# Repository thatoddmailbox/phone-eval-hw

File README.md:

# phone-eval-hw
The evaluation board for the [phone I built](https://github.com/thatoddmailbox/phone). [View PDF schematic](./thingb-eval-hw.pdf)

This was the first version of the hardware. The idea was to make sure that things were working in a more open (and therefore easier to assemble/test/debug) design before making a smaller, more portable version. It also allowed some problems to be caught and addressed for the next revision.

There are a [couple of known issues](https://github.com/thatoddmailbox/phone-eval-hw/issues/1) with this hardware. The biggest issue is that the battery charging IC, while theoretically capable of charging the battery at 1A, quickly gets too hot and throttles itself when charging. These issues were fixed in the [next revision](https://github.com/thatoddmailbox/phone-hw), which also had the correct form factor.

(note: this was originally called thingb-eval-hw because I thought I'd come up with a more creative name than "phone". I did not.)

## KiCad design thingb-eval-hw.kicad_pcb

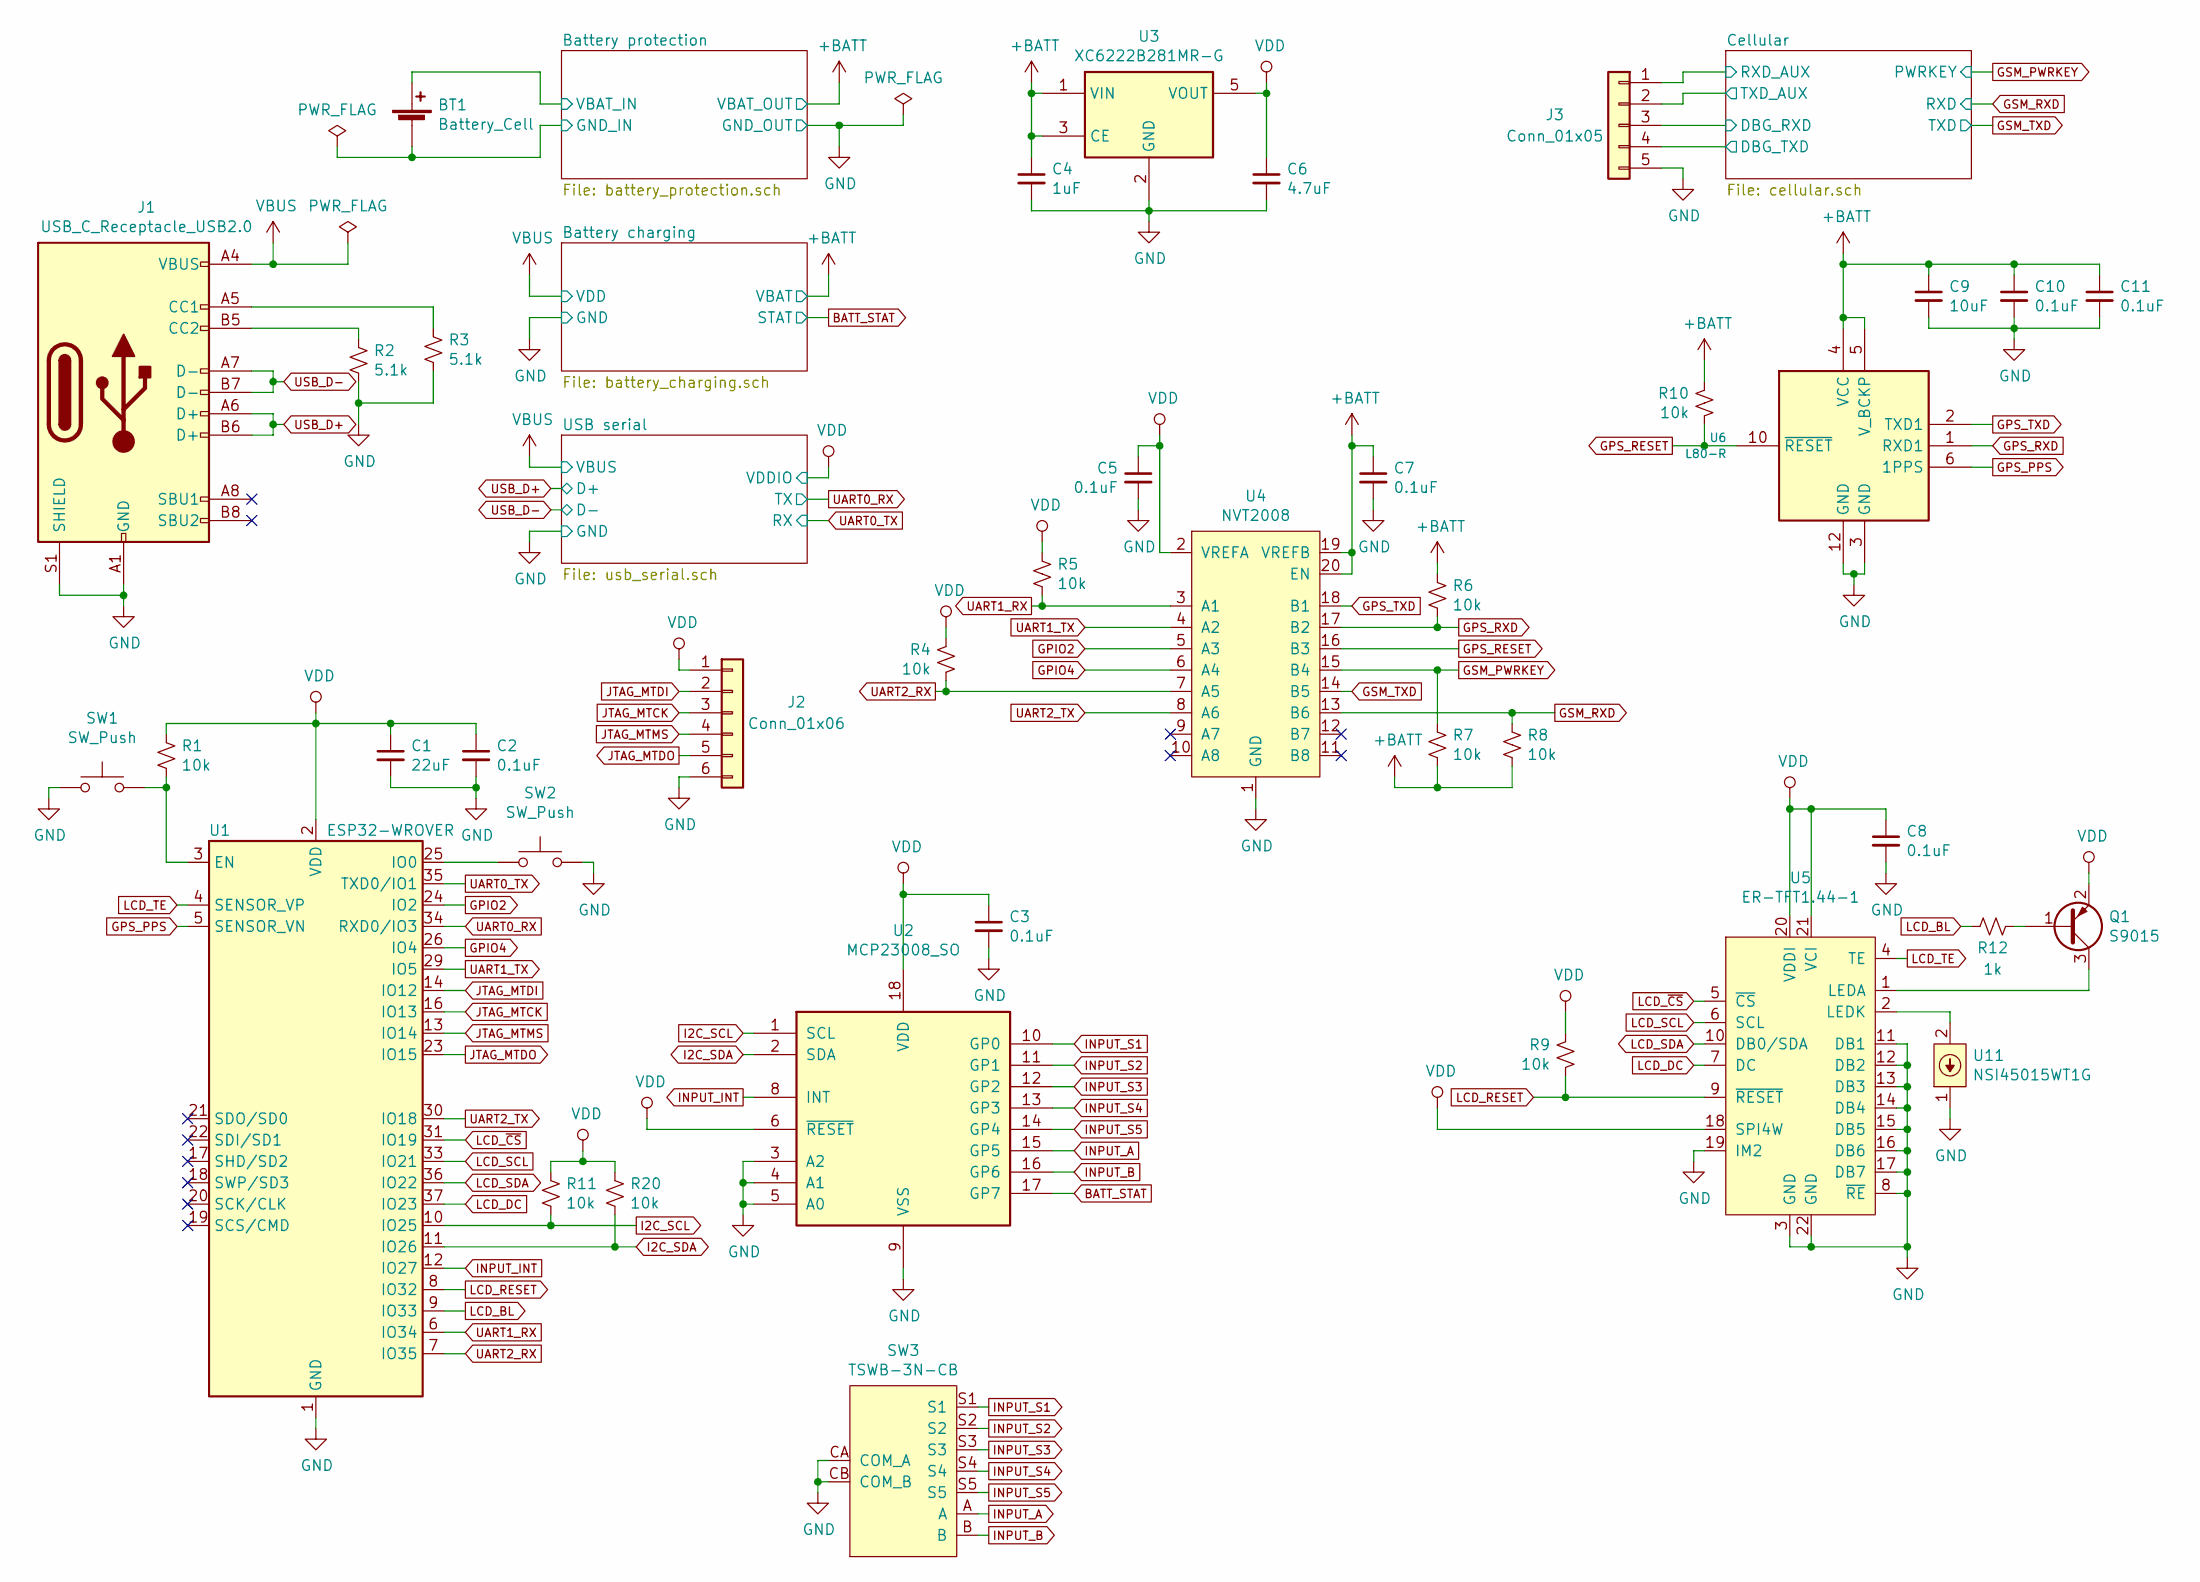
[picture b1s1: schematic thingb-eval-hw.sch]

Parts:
BT1: Battery_Cell; PinHeader_1x02_P2.54mm_Vertical
C1: 22uF; C_0603_1608Metric_Pad1.05x0.95mm_HandSolder
C2, C3, C5, C7, C8, C10, C11: 0.1uF; C_0603_1608Metric_Pad1.05x0.95mm_HandSolder
C4: 1uF; C_0603_1608Metric_Pad1.05x0.95mm_HandSolder
C6: 4.7uF; C_0603_1608Metric_Pad1.05x0.95mm_HandSolder
C9: 10uF; C_0603_1608Metric_Pad1.05x0.95mm_HandSolder
J1: USB_C_Receptacle_USB2.0; U262-16XN-4BVC11
J2: Conn_01x06; PinHeader_1x06_P2.54mm_Vertical
J3: Conn_01x05; PinHeader_1x05_P2.54mm_Vertical
Q1: S9015; SOT-23_Handsoldering
R1, R4, R5, R6, R7, R8, R9, R10, R11, R20: 10k; R_0603_1608Metric_Pad1.05x0.95mm_HandSolder
R2, R3: 5.1k; R_0603_1608Metric_Pad1.05x0.95mm_HandSolder
R12: 1k; R_0603_1608Metric_Pad1.05x0.95mm_HandSolder
SW1, SW2: SW_Push; SW_SPST_EVQPE1
SW3: TSWB-3N-CB
U1: ESP32-WROVER
U2: MCP23008_SO; SOIC-18W_7.5x11.6mm_P1.27mm
U3: XC6222B281MR-G; SOT-23-5
U4: NVT2008; TSSOP-20_4.4x6.5mm_P0.65mm
U5: ER-TFT1.44-1
U6: L80-R
U11: NSI45015WT1G; D_SOD-123

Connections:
+BATT: BT1.1 (+), C4.1, C7.1, C9.1, C10.1, C11.1, R6.1, R7.2, R8.2, R10.2, U3.1 (VIN), U3.3 (CE), U4.19 (VREFB), U4.20 (EN), U6.4 (VCC), U6.5 (V_BCKP); also elsewhere on the board
/Battery protection/GND_IN: BT1.2 (-); also elsewhere on the board
/Cellular/DBG_RXD: J3.3; also elsewhere on the board
/Cellular/DBG_TXD: J3.4; also elsewhere on the board
/Cellular/RXD_AUX: J3.1; also elsewhere on the board
/Cellular/TXD_AUX: J3.2; also elsewhere on the board
BATT_STAT: U2.17 (GP7); also elsewhere on the board
GND_OUT: C1.2, C2.2, C3.2, C4.2, C5.2, C6.2, C7.2, C8.2, C9.2, C10.2, C11.2, J1.A1 (GND), J1.A12 (GND), J1.B1 (GND), J1.B12 (GND), J1.S1 (SHIELD), J2.6, J3.5, R2.2, R3.2, SW1.2, SW2.2, SW3.CA (COM_A), SW3.CB (COM_B), U1.1 (GND), U1.15 (GND), U1.38 (GND), U2.3 (A2), U2.4 (A1), U2.5 (A0), U2.9 (VSS), U3.2 (GND), U4.1 (GND), U5.3 (GND), U5.8 (~RE), U5.11 (DB1), U5.12 (DB2), U5.13 (DB3), U5.14 (DB4), U5.15 (DB5), U5.16 (DB6), U5.17 (DB7), U5.19 (IM2), U5.22 (GND), U6.3 (GND), U6.12 (GND), U11.1; also elsewhere on the board
GPIO2: U1.24 (IO2), U4.5 (A3)
GPIO4: U1.26 (IO4), U4.6 (A4)
GPS_PPS: U1.5 (SENSOR_VN), U6.6 (1PPS)
GPS_RESET: R10.1, U4.16 (B3), U6.10 (~RESET)
GPS_RXD: R6.2, U4.17 (B2), U6.1 (RXD1)
GPS_TXD: U4.18 (B1), U6.2 (TXD1)
GSM_PWRKEY: R7.1, U4.15 (B4); also elsewhere on the board
GSM_RXD: R8.1, U4.13 (B6); also elsewhere on the board
GSM_TXD: U4.14 (B5); also elsewhere on the board
I2C_SCL: R11.2, U1.10 (IO25), U2.1 (SCL)
I2C_SDA: R20.2, U1.11 (IO26), U2.2 (SDA)
INPUT_A: SW3.A, U2.15 (GP5)
INPUT_B: SW3.B, U2.16 (GP6)
INPUT_INT: U1.12 (IO27), U2.8 (INT)
INPUT_S1: SW3.S1, U2.10 (GP0)
INPUT_S2: SW3.S2, U2.11 (GP1)
INPUT_S3: SW3.S3, U2.12 (GP2)
INPUT_S4: SW3.S4, U2.13 (GP3)
INPUT_S5: SW3.S5, U2.14 (GP4)
JTAG_MTCK: J2.3, U1.16 (IO13)
JTAG_MTDI: J2.2, U1.14 (IO12)
JTAG_MTDO: J2.5, U1.23 (IO15)
JTAG_MTMS: J2.4, U1.13 (IO14)
LCD_BL: R12.2, U1.9 (IO33)
LCD_DC: U1.37 (IO23), U5.7 (DC)
LCD_RESET: R9.1, U1.8 (IO32), U5.9 (~RESET)
LCD_SCL: U1.33 (IO21), U5.6 (SCL)
LCD_SDA: U1.36 (IO22), U5.10 (DB0/SDA)
LCD_TE: U1.4 (SENSOR_VP), U5.4 (TE)
LCD_~CS: U1.31 (IO19), U5.5 (~CS)
unnamed: J1.A5 (CC1), R3.1
unnamed: J1.B5 (CC2), R2.1
unnamed: Q1.1 (B), R12.1
unnamed: Q1.3 (C), U5.1 (LEDA)
unnamed: R1.2, SW1.1, U1.3 (EN)
unnamed: SW2.1, U1.25 (IO0)
unnamed: U5.2 (LEDK), U11.2
UART0_RX: U1.34 (RXD0/IO3); also elsewhere on the board
UART0_TX: U1.35 (TXD0/IO1); also elsewhere on the board
UART1_RX: R5.2, U1.6 (IO34), U4.3 (A1)
UART1_TX: U1.29 (IO5), U4.4 (A2)
UART2_RX: R4.2, U1.7 (IO35), U4.7 (A5)
UART2_TX: U1.30 (IO18), U4.8 (A6)
USB_D+: J1.A6 (D+), J1.B6 (D+); also elsewhere on the board
USB_D-: J1.A7 (D-), J1.B7 (D-); also elsewhere on the board
VBUS: J1.A4 (VBUS), J1.A9 (VBUS), J1.B4 (VBUS), J1.B9 (VBUS); also elsewhere on the board
VDD: C1.1, C2.1, C3.1, C5.1, C6.1, C8.1, J2.1, Q1.2 (E), R1.1, R4.1, R5.1, R9.2, R11.1, R20.1, U1.2 (VDD), U2.6 (~RESET~), U2.18 (VDD), U3.5 (VOUT), U4.2 (VREFA), U5.18 (SPI4W), U5.20 (VDDI), U5.21 (VCI); also elsewhere on the board

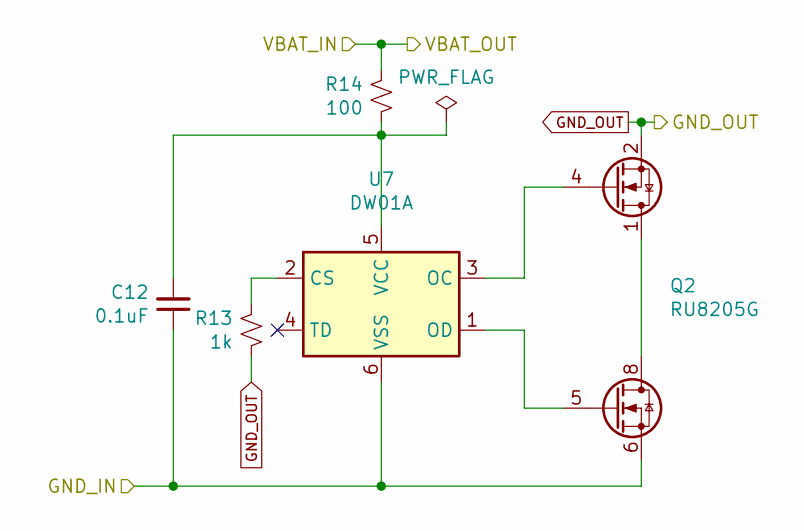
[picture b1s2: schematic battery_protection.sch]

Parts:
C12: 0.1uF; C_0603_1608Metric_Pad1.05x0.95mm_HandSolder
Q2: RU8205G; TSSOP-8_4.4x3mm_P0.65mm
R13: 1k; R_0603_1608Metric_Pad1.05x0.95mm_HandSolder
R14: 100; R_0603_1608Metric_Pad1.05x0.95mm_HandSolder
U7: DW01A; SOT-23-6

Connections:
+BATT: R14.2; also elsewhere on the board
/Battery protection/GND_IN: C12.1, Q2.6 (S2), Q2.7 (S2), U7.6 (VSS); also elsewhere on the board
GND_OUT: Q2.2 (S1), Q2.3 (S1), R13.1; also elsewhere on the board
unnamed: C12.2, R14.1, U7.5 (VCC)
unnamed: Q2.1 (D1), Q2.8 (D2)
unnamed: Q2.4 (G1), U7.3 (OC)
unnamed: Q2.5 (G2), U7.1 (OD)
unnamed: R13.2, U7.2 (CS)

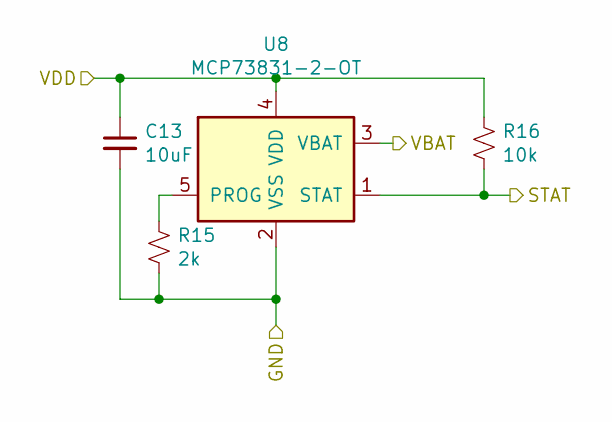
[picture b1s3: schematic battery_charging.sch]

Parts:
C13: 10uF; C_0603_1608Metric_Pad1.05x0.95mm_HandSolder
R15: 2k; R_0603_1608Metric_Pad1.05x0.95mm_HandSolder
R16: 10k; R_0603_1608Metric_Pad1.05x0.95mm_HandSolder
U8: MCP73831-2-OT; SOT-23-5

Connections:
+BATT: U8.3 (VBAT); also elsewhere on the board
BATT_STAT: R16.2, U8.1 (STAT); also elsewhere on the board
GND_OUT: C13.2, R15.2, U8.2 (VSS); also elsewhere on the board
unnamed: R15.1, U8.5 (PROG)
VBUS: C13.1, R16.1, U8.4 (VDD); also elsewhere on the board

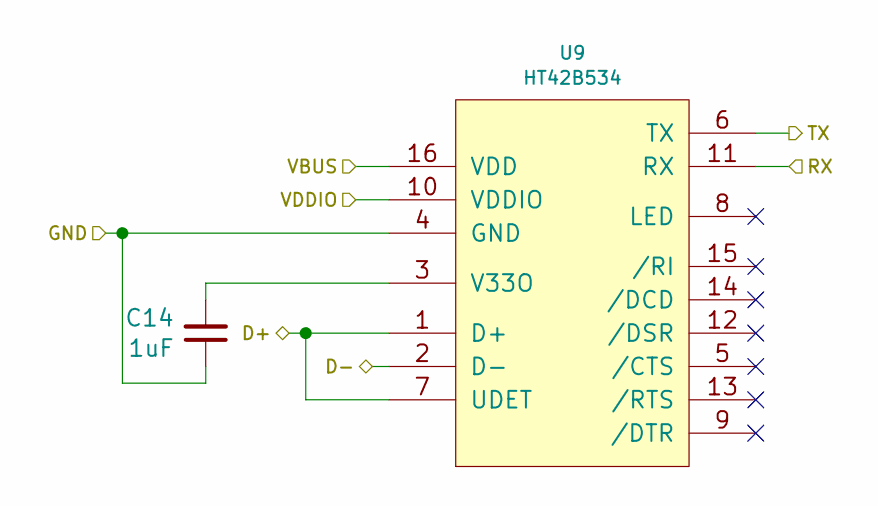
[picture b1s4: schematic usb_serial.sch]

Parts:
C14: 1uF; C_0603_1608Metric_Pad1.05x0.95mm_HandSolder
U9: HT42B534; SOIC-16_3.9x9.9mm_P1.27mm

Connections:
GND_OUT: C14.1, U9.4 (GND); also elsewhere on the board
unnamed: C14.2, U9.3 (V33O)
UART0_RX: U9.6 (TX); also elsewhere on the board
UART0_TX: U9.11 (RX); also elsewhere on the board
USB_D+: U9.1 (D+), U9.7 (UDET); also elsewhere on the board
USB_D-: U9.2 (D-); also elsewhere on the board
VBUS: U9.16 (VDD); also elsewhere on the board
VDD: U9.10 (VDDIO); also elsewhere on the board

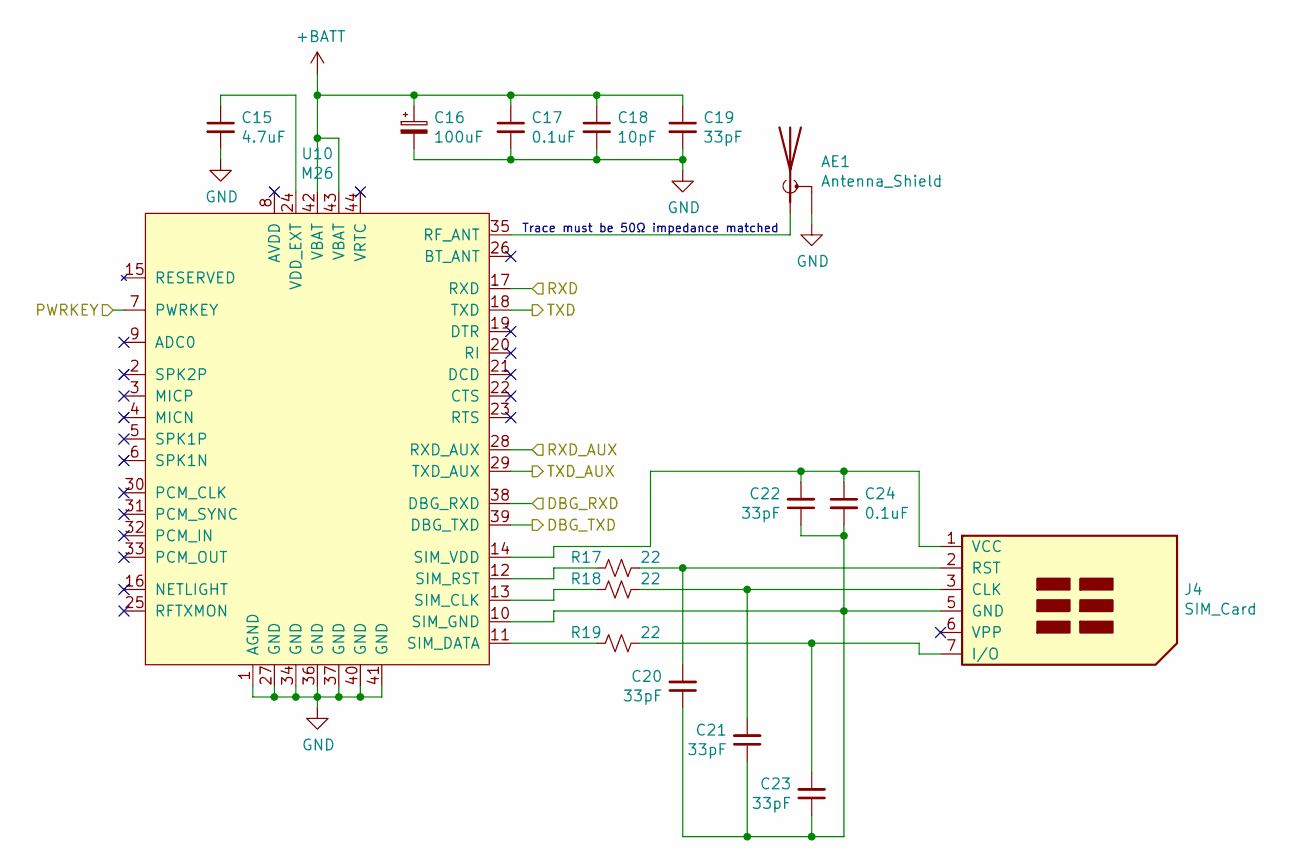
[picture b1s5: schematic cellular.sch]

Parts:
AE1: Antenna_Shield; U.FL_Molex_MCRF_73412-0110_Vertical
C15: 4.7uF; C_0603_1608Metric_Pad1.05x0.95mm_HandSolder
C16: 100uF; CP_EIA-3528-15_AVX-H_Pad1.50x2.35mm_HandSolder
C17, C24: 0.1uF; C_0603_1608Metric_Pad1.05x0.95mm_HandSolder
C18: 10pF; C_0603_1608Metric_Pad1.05x0.95mm_HandSolder
C19, C20, C21, C22, C23: 33pF; C_0603_1608Metric_Pad1.05x0.95mm_HandSolder
J4: SIM_Card; 7112S0815X19LF
R17, R18, R19: 22; R_0603_1608Metric_Pad1.05x0.95mm_HandSolder
U10: M26

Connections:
+BATT: C16.1, C17.1, C18.1, C19.1, U10.42 (VBAT), U10.43 (VBAT); also elsewhere on the board
/Cellular/DBG_RXD: U10.38 (DBG_RXD); also elsewhere on the board
/Cellular/DBG_TXD: U10.39 (DBG_TXD); also elsewhere on the board
/Cellular/RXD_AUX: U10.28 (RXD_AUX); also elsewhere on the board
/Cellular/TXD_AUX: U10.29 (TXD_AUX); also elsewhere on the board
GND_OUT: AE1.2 (Shield), C15.2, C16.2, C17.2, C18.2, C19.2, U10.1 (AGND), U10.27 (GND), U10.34 (GND), U10.36 (GND), U10.37 (GND), U10.40 (GND), U10.41 (GND); also elsewhere on the board
GSM_PWRKEY: U10.7 (PWRKEY); also elsewhere on the board
GSM_RXD: U10.17 (RXD); also elsewhere on the board
GSM_TXD: U10.18 (TXD); also elsewhere on the board
unnamed: AE1.1 (A), U10.35 (RF_ANT)
unnamed: C15.1, U10.24 (VDD_EXT)
unnamed: C20.1, C21.1, C22.1, C23.1, C24.2, J4.5 (GND), U10.10 (SIM_GND)
unnamed: C20.2, J4.2 (RST), R17.1
unnamed: C21.2, J4.3 (CLK), R18.1
unnamed: C22.2, C24.1, J4.1 (VCC), U10.14 (SIM_VDD)
unnamed: C23.2, J4.7 (I/O), R19.1
unnamed: R17.2, U10.12 (SIM_RST)
unnamed: R18.2, U10.13 (SIM_CLK)
unnamed: R19.2, U10.11 (SIM_DATA)

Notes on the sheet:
Trace must be 50Ω impedance matched

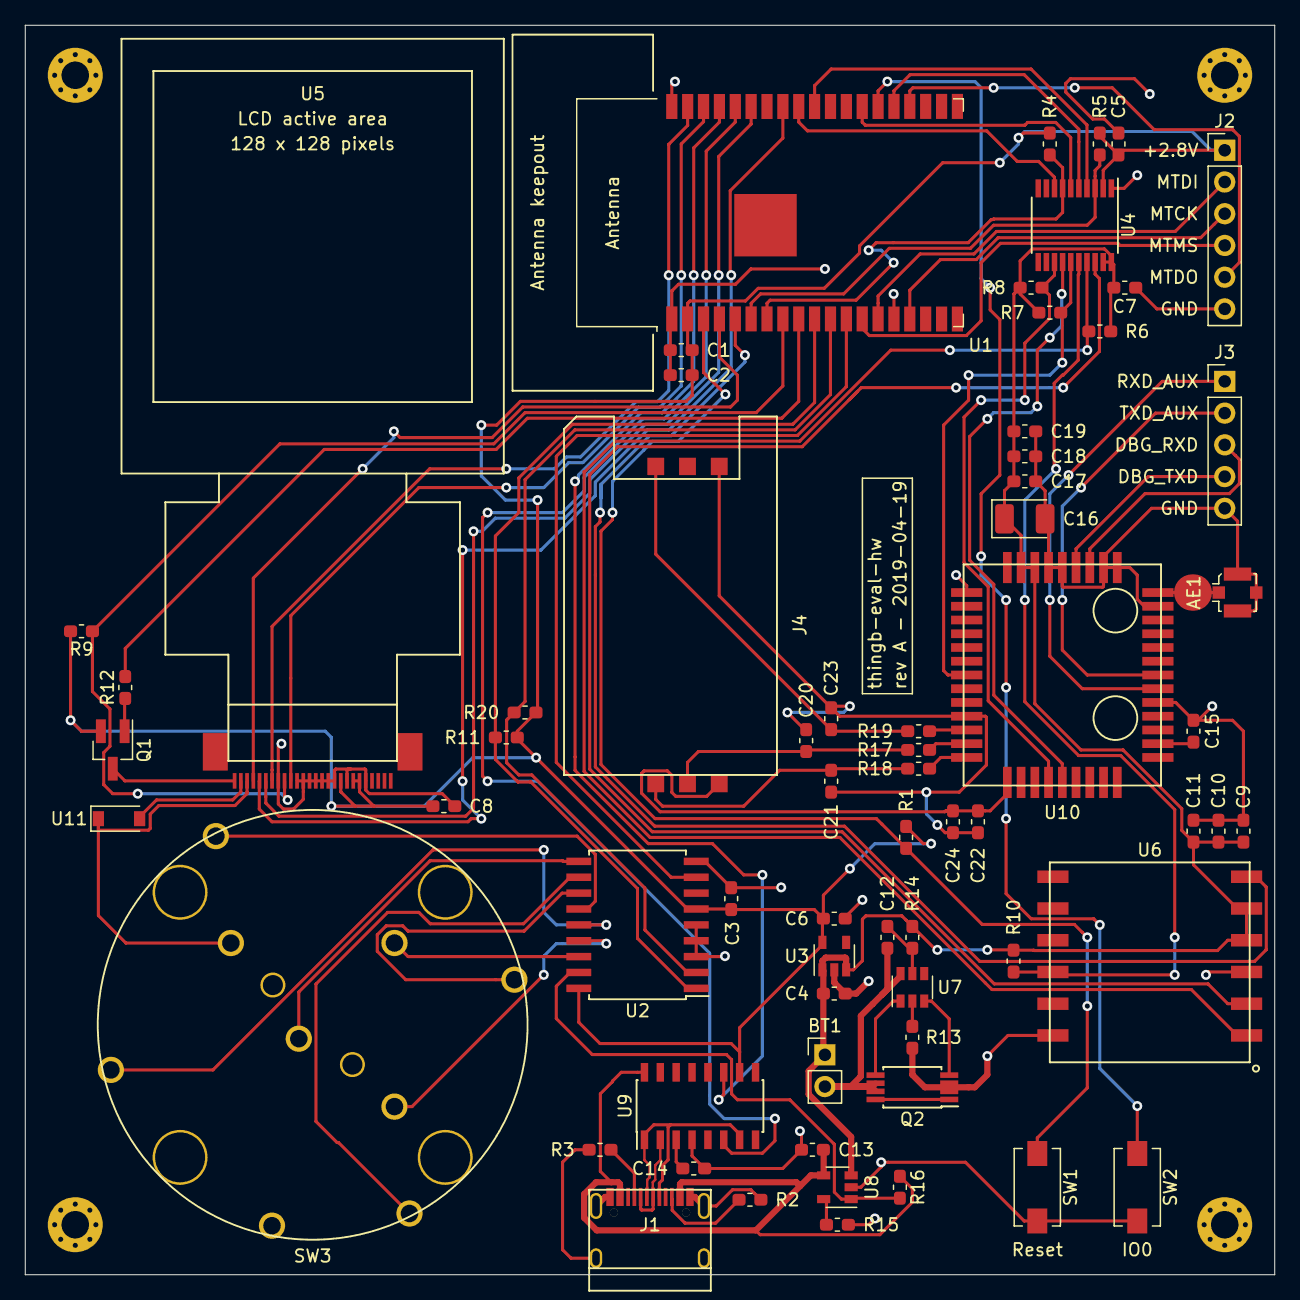
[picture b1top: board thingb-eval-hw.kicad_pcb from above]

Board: 2 copper layers, 100.0 x 100.0 mm, 66 parts (0 on the bottom side), 72 nets.

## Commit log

2019-03-24 commit current schematics
2019-03-25 add new navigation switch symbol and footprint, remove duplicate L80 footprint
2019-03-26 add symbol and footprint for quectel m26 module
2019-03-27 reorder sim card pins on quectel m26 symbol to match the kicad sim card symbol's order
2019-03-27 add symbols and footprints for eastrising tft display and its connector
2019-03-28 add symbol for nvt2008 level shifter
2019-03-29 add cellular module, input, display, level shifter, and more to schematic
2019-03-30 add port expander symbols
2019-03-30 fix esp32-wrover symbol
2019-03-30 rearrange sim card pins on m26 symbol
2019-03-30 lots of improvements to schematic: fixing decoupling, matching reference designs and recommendations better, connecting pins to esp32 and adding i2c gpio expander
2019-03-30 add dw01a and 8205 symbols
2019-03-30 change battery protection to dw01 and 8205 pair
2019-03-30 annotate schematic
2019-03-30 add generated HTML BOM files to gitignore
2019-03-30 remove ap9101 symbols
2019-03-30 fix power flag things
2019-03-31 add transistor to control led backlist and flip led anode and cathode positions on tft symbol
2019-03-31 add footprint for usb type-c connector
2019-03-31 reannotate schematic
2019-03-31 add missing holes to usb type-c connector footprint
2019-03-31 add footprint for sim card holder
2019-03-31 associate footprints with all parts
2019-04-01 add nsi45015wt1g constant current led driver symbol
2019-04-01 replace backlight resistor with 15 mA constant-current driver, to ensure screen brightness is consistent as battery depletes
2019-04-04 switch button footprints to be smd switches
2019-04-09 add power pins to debugging headers and rename usb nets so that kicad recognizes them as a differential pair
2019-04-15 i am dumb and forgot pullups on the i2c lines
2019-04-15 lengthen pads of usb-c connector as suggested by datasheet for subsitute part
    https://datasheet.lcsc.com/szlcsc/1903211732_Korean-Hroparts-Elec-TYPE-C-31-M-12_C165948.pdf
2019-04-20 switch programming resistor on lipo charger because it apparently maxes at 500 mA current
2019-04-20 more weird usb-c port footprint changes
2019-04-20 start work on footprint for folded tft module but give up
2019-04-20 modify esp32-wrover footprint to indicate antenna keepout in silkscreen
2019-04-20 add routed pcb layout
2019-04-20 add name, date, and revision to silkscreen
2019-04-20 update version of esp32-wrover footprint used in pcb layout
2019-04-20 actually i'm ordering them today
2019-04-20 generate gerbers
2020-08-29 add PDF schematic
2020-08-29 add README
2020-08-29 add LICENSE
